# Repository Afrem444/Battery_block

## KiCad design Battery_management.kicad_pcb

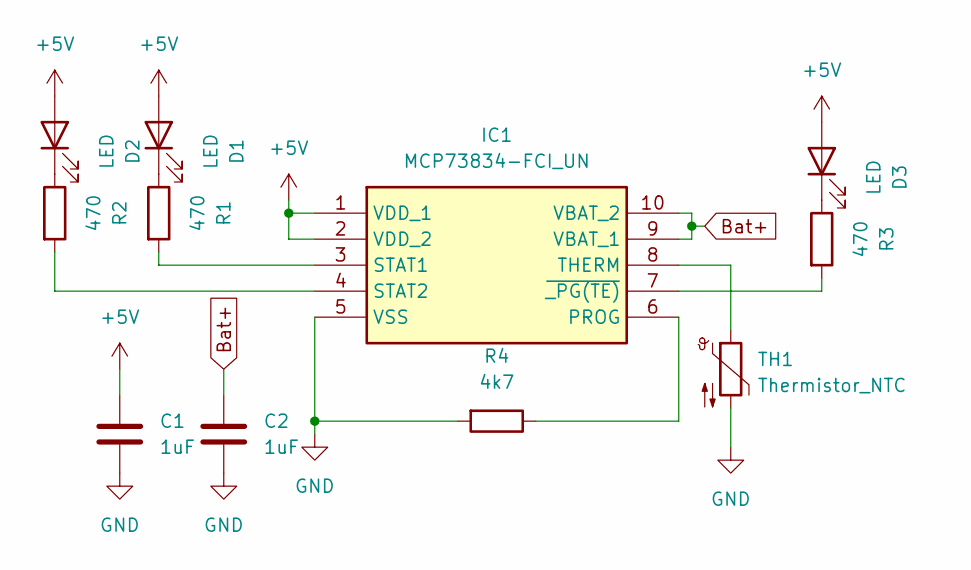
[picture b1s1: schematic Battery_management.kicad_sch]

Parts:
C1, C2: 1uF; C_0402_1005Metric_Pad0.74x0.62mm_HandSolder
D1, D2, D3: LED; LED_0402_1005Metric_Pad0.77x0.64mm_HandSolder
IC1: MCP73834-FCI_UN; SOP50P490X110-10N; Mouser Part Number 579-MCP73834-FCI/UN
R1, R2, R3: 470; R_0402_1005Metric_Pad0.72x0.64mm_HandSolder
R4: 4k7; R_0402_1005Metric_Pad0.72x0.64mm_HandSolder
TH1: Thermistor_NTC; R_0402_1005Metric_Pad0.72x0.64mm_HandSolder

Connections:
+5V: C1.1, D1.2 (A), D2.2 (A), D3.2 (A), IC1.1 (VDD_1), IC1.2 (VDD_2)
Bat+: C2.1, IC1.9 (VBAT_1), IC1.10 (VBAT_2)
GND: C1.2, C2.2, IC1.5 (VSS), R4.2, TH1.2
unnamed: D1.1 (K), R1.1
unnamed: D2.1 (K), R2.1
unnamed: D3.1 (K), R3.1
unnamed: IC1.6 (PROG), R4.1
unnamed: IC1.3 (STAT1), R1.2
unnamed: IC1.4 (STAT2), R2.2
unnamed: IC1.8 (THERM), TH1.1
unnamed: IC1.7 (~_PG(TE)), R3.2

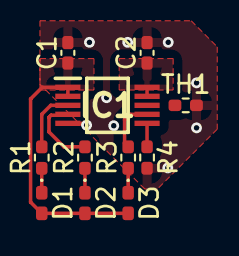
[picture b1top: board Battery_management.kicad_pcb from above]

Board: 2 copper layers, 11 parts (0 on the bottom side), 11 nets.

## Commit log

2025-12-05 Create .gitignore for KiCad project
    Add a .gitignore file for KiCad project files and temporary files.
2025-12-05 Add 0402 version
